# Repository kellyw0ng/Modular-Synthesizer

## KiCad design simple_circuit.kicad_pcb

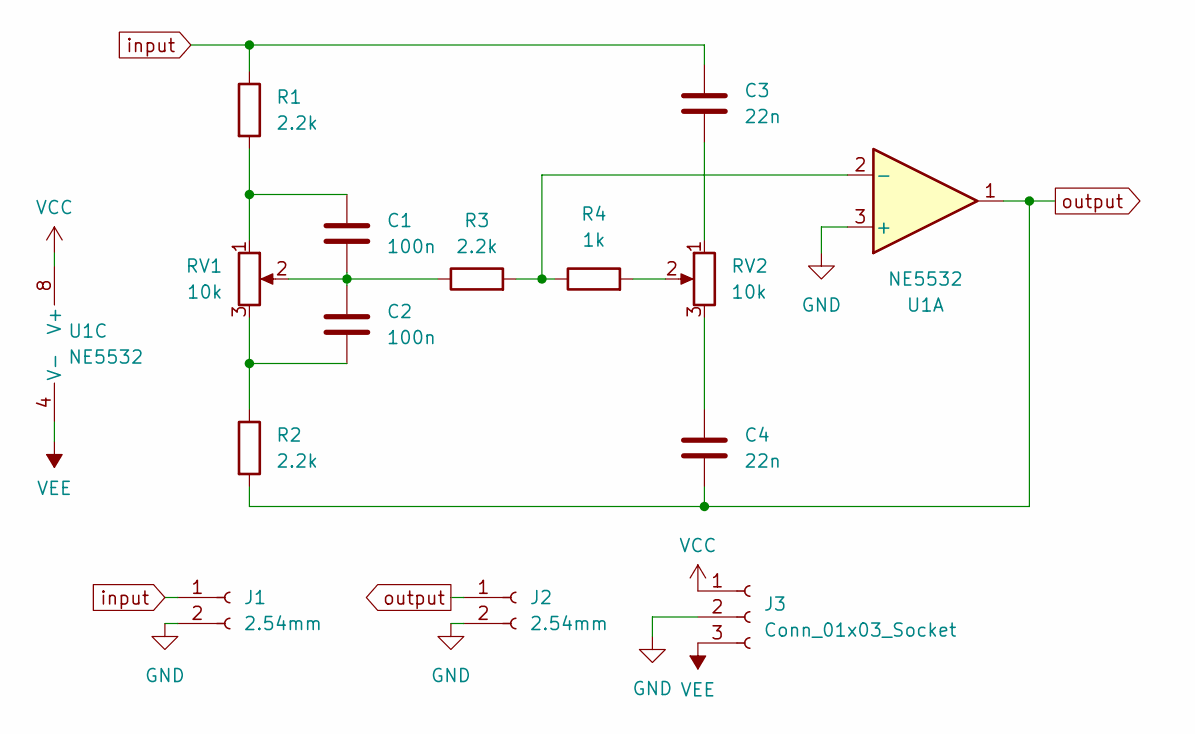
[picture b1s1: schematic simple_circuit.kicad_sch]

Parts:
C1, C2: 100n; C_Disc_D5.0mm_W2.5mm_P5.00mm
C3: 22n; C_Disc_D5.0mm_W2.5mm_P5.00mm
C4: 22n; C_Disc_D5.0mm_W2.5mm_P2.50mm
J1, J2: 2.54mm; PinSocket_1x02_P2.54mm_Vertical
J3: Conn_01x03_Socket; PinSocket_1x03_P2.54mm_Vertical
R1, R2, R3: 2.2k; R_Axial_DIN0207_L6.3mm_D2.5mm_P10.16mm_Horizontal
R4: 1k; R_Axial_DIN0207_L6.3mm_D2.5mm_P10.16mm_Horizontal
RV1, RV2: 10k; Potentiometer_Piher_PT-6-V_Vertical
U1: NE5532; DIP-8_W7.62mm_Socket

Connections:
GND: J1.2, J2.2, J3.2, U1.3 (+)
unnamed: C1.1, R1.2, RV1.1
unnamed: C1.2, C2.1, R3.1, RV1.2
unnamed: C2.2, R2.1, RV1.3
unnamed: C3.2, RV2.1
unnamed: C4.1, RV2.3
unnamed: R4.2, RV2.2
unnamed: R3.2, R4.1, U1.2 (-)
VCC: J3.1, U1.8 (V+)
VEE: J3.3, U1.4 (V-)
input: C3.1, J1.1, R1.1
output: C4.2, J2.1, R2.2, U1.1

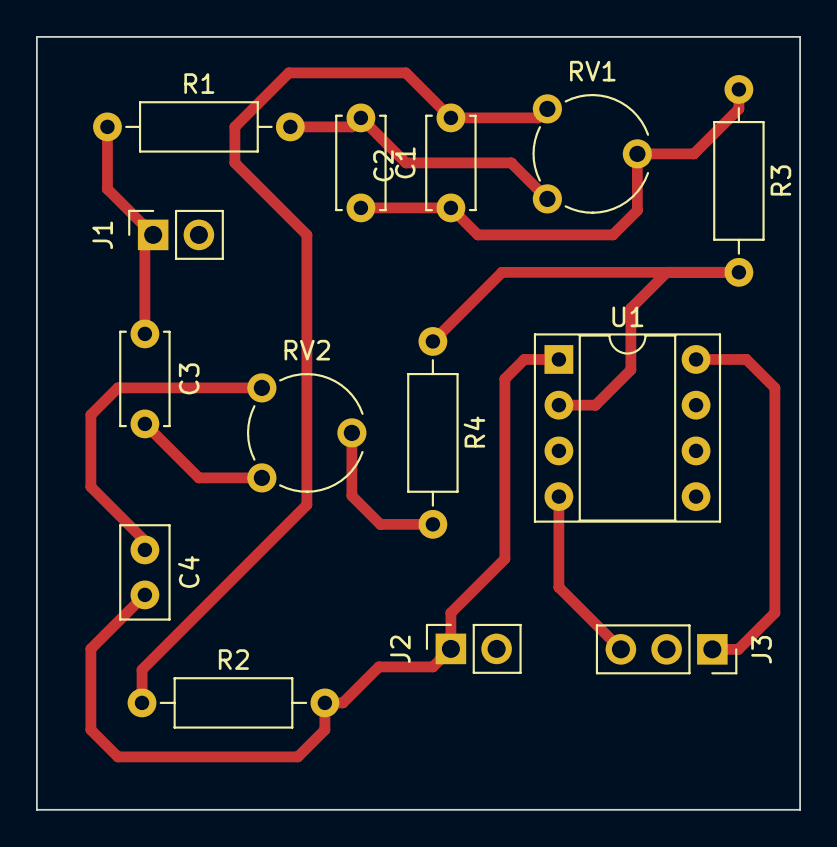
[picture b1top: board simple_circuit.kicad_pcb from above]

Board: 2 copper layers, 42.4 x 42.9 mm, 14 parts (0 on the bottom side), 12 nets.
